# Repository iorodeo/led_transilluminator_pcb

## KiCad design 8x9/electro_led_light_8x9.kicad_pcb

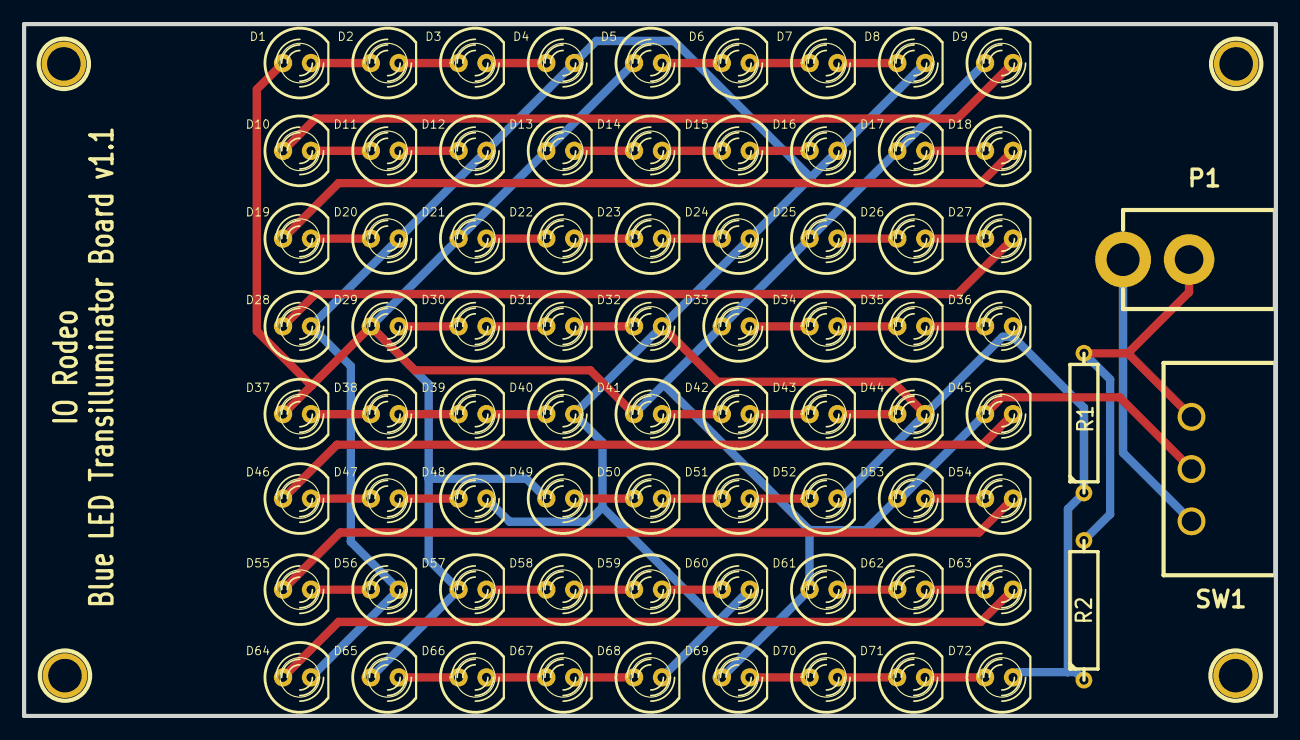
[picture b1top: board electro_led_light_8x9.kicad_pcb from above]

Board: 2 copper layers, 113.8 x 62.9 mm, 80 parts (0 on the bottom side), 58 nets.

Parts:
D1, D2, D3, D4, D5, D6, D7, D8, D9, D10, D11, D12, D13, D14, D15, D16, D17, D18, D19, D20, D21, D22, D23, D24, D25, D26, D27, D28, D29, D30, D31, D32, D33, D34, D35, D36, D37, D38, D39, D40, D41, D42, D43, D44, D45, D46, D47, D48, D49, D50, D51, D52, D53, D54, D55, D56, D57, D58, D59, D60, D61, D62, D63, D64, D65, D66, D67, D68, D69, D70, D71, D72: LED; CUSTOM2 LED-5MM
M1, M2, M3, M4: P***; 1pin
P1: CONN_2; DCJACK_2PIN
R1, R2: R; R5
SW1: SWITCH_INV; slide_switch

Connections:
/15V: P1.1, SW1.1
GND: P1.2, R1.2, R2.2, SW1.3
unnamed: D1.2, D2.1
unnamed: D25.2, D26.1
unnamed: D9.2, D10.1
unnamed: D10.2, D11.1
unnamed: D11.2, D12.1
unnamed: D15.2, D16.1
unnamed: D14.2, D15.1
unnamed: D13.2, D14.1
unnamed: D5.2, D6.1
unnamed: D6.2, D7.1
unnamed: D7.2, D8.1
unnamed: D3.2, D4.1
unnamed: D2.2, D3.1
unnamed: D4.2, D8.2, D12.2, D16.2, D20.2, D24.2, D28.2, D32.2, D36.2, D40.2, D44.2, D48.2, D52.2, D56.2, D60.2, D64.2, D68.2, D72.2, R1.1, R2.1
unnamed: D1.1, D5.1, D9.1, D13.1, D17.1, D21.1, D25.1, D29.1, D33.1, D37.1, D41.1, D45.1, D49.1, D53.1, D57.1, D61.1, D65.1, D69.1, SW1.2
unnamed: D69.2, D70.1
unnamed: D33.2, D34.1
unnamed: D34.2, D35.1
unnamed: D35.2, D36.1
unnamed: D39.2, D40.1
unnamed: D38.2, D39.1
unnamed: D37.2, D38.1
unnamed: D45.2, D46.1
unnamed: D46.2, D47.1
unnamed: D47.2, D48.1
unnamed: D43.2, D44.1
unnamed: D42.2, D43.1
unnamed: D41.2, D42.1
unnamed: D67.2, D68.1
unnamed: D66.2, D67.1
unnamed: D65.2, D66.1
unnamed: D71.2, D72.1
unnamed: D70.2, D71.1
unnamed: D49.2, D50.1
unnamed: D17.2, D18.1
unnamed: D18.2, D19.1
unnamed: D19.2, D20.1
unnamed: D23.2, D24.1
unnamed: D22.2, D23.1
unnamed: D21.2, D22.1
unnamed: D29.2, D30.1
unnamed: D30.2, D31.1
unnamed: D31.2, D32.1
unnamed: D27.2, D28.1
unnamed: D26.2, D27.1
unnamed: D57.2, D58.1
unnamed: D58.2, D59.1
unnamed: D59.2, D60.1
unnamed: D63.2, D64.1
unnamed: D62.2, D63.1
unnamed: D61.2, D62.1
unnamed: D53.2, D54.1
unnamed: D54.2, D55.1
unnamed: D55.2, D56.1
unnamed: D51.2, D52.1
unnamed: D50.2, D51.1

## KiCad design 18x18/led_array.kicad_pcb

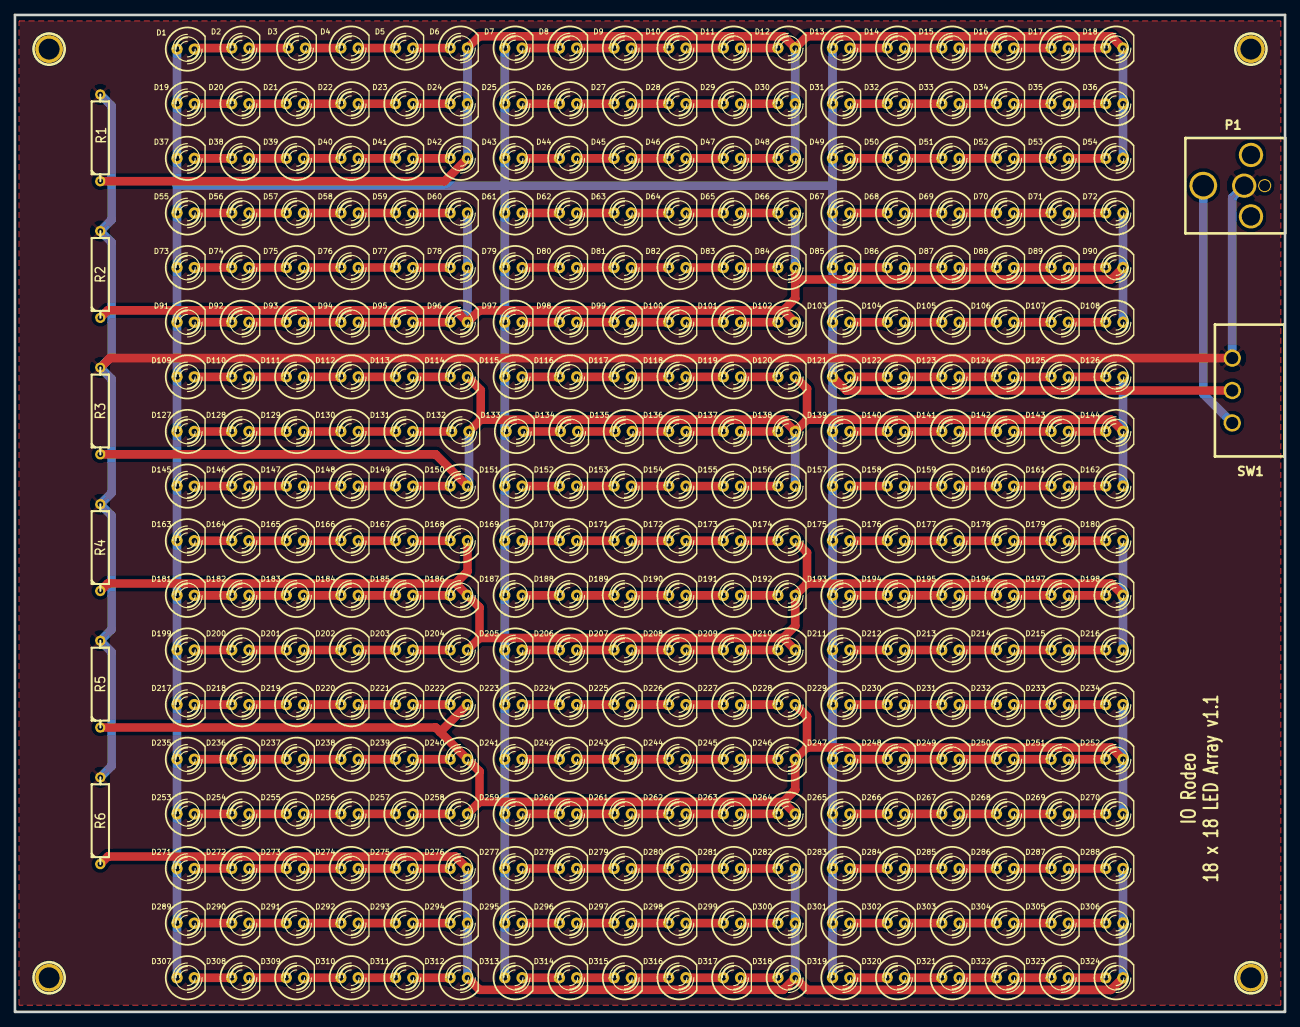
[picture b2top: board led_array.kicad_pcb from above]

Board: 2 copper layers, 186.0 x 146.0 mm, 336 parts (0 on the bottom side), 279 nets.

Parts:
D1, D2, D3, D4, D5, D6, D7, D8, D9, D10, D11, D12, D13, D14, D15, D16, D17, D18, D19, D20, D21, D22, D23, D24, D25, D26, D27, D28, D29, D30, D31, D32, D33, D34, D35, D36, D37, D38, D39, D40, D41, D42, D43, D44, D45, D46, D47, D48, D49, D50, D51, D52, D53, D54, D55, D56, D57, D58, D59, D60, D61, D62, D63, D64, D65, D66, D67, D68, D69, D70, D71, D72, D73, D74, D75, D76, D77, D78, D79, D80, D81, D82, D83, D84, D85, D86, D87, D88, D89, D90, D91, D92, D93, D94, D95, D96, D97, D98, D99, D100, D101, D102, D103, D104, D105, D106, D107, D108, D109, D110, D111, D112, D113, D114, D115, D116, D117, D118, D119, D120, D121, D122, D123, D124, D125, D126, D127, D128, D129, D130, D131, D132, D133, D134, D135, D136, D137, D138, D139, D140, D141, D142, D143, D144, D145, D146, D147, D148, D149, D150, D151, D152, D153, D154, D155, D156, D157, D158, D159, D160, D161, D162, D163, D164, D165, D166, D167, D168, D169, D170, D171, D172, D173, D174, D175, D176, D177, D178, D179, D180, D181, D182, D183, D184, D185, D186, D187, D188, D189, D190, D191, D192, D193, D194, D195, D196, D197, D198, D199, D200, D201, D202, D203, D204, D205, D206, D207, D208, D209, D210, D211, D212, D213, D214, D215, D216, D217, D218, D219, D220, D221, D222, D223, D224, D225, D226, D227, D228, D229, D230, D231, D232, D233, D234, D235, D236, D237, D238, D239, D240, D241, D242, D243, D244, D245, D246, D247, D248, D249, D250, D251, D252, D253, D254, D255, D256, D257, D258, D259, D260, D261, D262, D263, D264, D265, D266, D267, D268, D269, D270, D271, D272, D273, D274, D275, D276, D277, D278, D279, D280, D281, D282, D283, D284, D285, D286, D287, D288, D289, D290, D291, D292, D293, D294, D295, D296, D297, D298, D299, D300, D301, D302, D303, D304, D305, D306, D307, D308, D309, D310, D311, D312, D313, D314, D315, D316, D317, D318, D319, D320, D321, D322, D323, D324: LED; CUSTOM2 LED-5MM
M1, M2, M3, M4: P***; 1pin
P1: CONN_2; DCJACK_2PIN_HIGHCURRENT
R1, R2, R3, R4, R5, R6: R; R5
SW1: SWITCH_INV; slide_switch

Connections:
/15V: P1.1, SW1.1
GND: P1.2, R1.2, R2.2, R3.2, R4.2, R5.2, R6.2, SW1.3
unnamed: D265.2, D266.1
unnamed: D266.2, D267.1
unnamed: D267.2, D268.1
unnamed: D191.2, D192.1
unnamed: D202.2, D203.1
unnamed: D203.2, D204.1
unnamed: D197.2, D198.1
unnamed: D196.2, D197.1
unnamed: D172.2, D173.1
unnamed: D173.2, D174.1
unnamed: D179.2, D180.1
unnamed: D178.2, D179.1
unnamed: D166.2, D167.1
unnamed: D167.2, D168.1
unnamed: D214.2, D215.1
unnamed: D215.2, D216.1
unnamed: D208.2, D209.1
unnamed: D209.2, D210.1
unnamed: D253.2, D254.1
unnamed: D254.2, D255.1
unnamed: D229.2, D230.1
unnamed: D230.2, D231.1
unnamed: D231.2, D232.1
unnamed: D232.2, D233.1
unnamed: D237.2, D238.1
unnamed: D238.2, D239.1
unnamed: D236.2, D237.1
unnamed: D235.2, D236.1
unnamed: D223.2, D224.1
unnamed: D224.2, D225.1
unnamed: D225.2, D226.1
unnamed: D226.2, D227.1
unnamed: D219.2, D220.1
unnamed: D268.2, D269.1
unnamed: D241.2, D242.1
unnamed: D242.2, D243.1
unnamed: D243.2, D244.1
unnamed: D244.2, D245.1
unnamed: D249.2, D250.1
unnamed: D250.2, D251.1
unnamed: D248.2, D249.1
unnamed: D247.2, D248.1
unnamed: D259.2, D260.1
unnamed: D260.2, D261.1
unnamed: D261.2, D262.1
unnamed: D262.2, D263.1
unnamed: D255.2, D256.1
unnamed: D256.2, D257.1
unnamed: D188.2, D189.1
unnamed: D189.2, D190.1
unnamed: D190.2, D191.1
unnamed: D195.2, D196.1
unnamed: D194.2, D195.1
unnamed: D193.2, D194.1
unnamed: D205.2, D206.1
unnamed: D206.2, D207.1
unnamed: D207.2, D208.1
unnamed: D201.2, D202.1
unnamed: D200.2, D201.1
unnamed: D199.2, D200.1
unnamed: D168.2, D174.2, D180.2, D186.2, D192.2, D198.2, D204.2, D210.2, D216.2, R4.1
unnamed: D211.2, D212.1
unnamed: D212.2, D213.1
unnamed: D213.2, D214.1
unnamed: D187.2, D188.1
unnamed: D163.2, D164.1
unnamed: D184.2, D185.1
unnamed: D185.2, D186.1
unnamed: D175.2, D176.1
unnamed: D176.2, D177.1
unnamed: D177.2, D178.1
unnamed: D183.2, D184.1
unnamed: D182.2, D183.1
unnamed: D181.2, D182.1
unnamed: D169.2, D170.1
unnamed: D170.2, D171.1
unnamed: D171.2, D172.1
unnamed: D165.2, D166.1
unnamed: D164.2, D165.1
unnamed: D278.2, D279.1
unnamed: D279.2, D280.1
unnamed: D280.2, D281.1
unnamed: D273.2, D274.1
unnamed: D274.2, D275.1
unnamed: D272.2, D273.1
unnamed: D271.2, D272.1
unnamed: D316.2, D317.1
unnamed: D309.2, D310.1
unnamed: D310.2, D311.1
unnamed: D308.2, D309.1
unnamed: D307.2, D308.1
unnamed: D283.2, D284.1
unnamed: D284.2, D285.1
unnamed: D285.2, D286.1
unnamed: D286.2, D287.1
unnamed: D291.2, D292.1
unnamed: D292.2, D293.1
unnamed: D290.2, D291.1
unnamed: D289.2, D290.1
unnamed: D277.2, D278.1
unnamed: D275.2, D276.1
unnamed: D322.2, D323.1
unnamed: D323.2, D324.1
unnamed: D317.2, D318.1
unnamed: D276.2, D282.2, D288.2, D294.2, D300.2, D306.2, D312.2, D318.2, D324.2, R6.1
unnamed: D293.2, D294.1
unnamed: D299.2, D300.1
unnamed: D298.2, D299.1
unnamed: D311.2, D312.1
unnamed: D305.2, D306.1
unnamed: D304.2, D305.1
unnamed: D281.2, D282.1
unnamed: D287.2, D288.1
unnamed: D239.2, D240.1
unnamed: D245.2, D246.1
unnamed: D257.2, D258.1
unnamed: D251.2, D252.1
unnamed: D227.2, D228.1
unnamed: D222.2, D228.2, D234.2, D240.2, D246.2, D252.2, D258.2, D264.2, D270.2, R5.1
unnamed: D233.2, D234.1
unnamed: D220.2, D221.1
unnamed: D221.2, D222.1
unnamed: D269.2, D270.1
unnamed: D218.2, D219.1
unnamed: D217.2, D218.1
unnamed: D319.2, D320.1
unnamed: D320.2, D321.1
unnamed: D321.2, D322.1
unnamed: D295.2, D296.1
unnamed: D296.2, D297.1
unnamed: D297.2, D298.1
unnamed: D303.2, D304.1
unnamed: D302.2, D303.1
unnamed: D301.2, D302.1
unnamed: D313.2, D314.1
unnamed: D314.2, D315.1
unnamed: D315.2, D316.1
unnamed: D263.2, D264.1
unnamed: D17.2, D18.1
unnamed: D4.2, D5.1
unnamed: D5.2, D6.1
unnamed: D52.2, D53.1
unnamed: D53.2, D54.1
unnamed: D46.2, D47.1
unnamed: D47.2, D48.1
unnamed: D22.2, D23.1
unnamed: D23.2, D24.1
unnamed: D29.2, D30.1
unnamed: D28.2, D29.1
unnamed: D40.2, D41.1
unnamed: D41.2, D42.1
unnamed: D35.2, D36.1
unnamed: D34.2, D35.1
unnamed: D10.2, D11.1
unnamed: D11.2, D12.1
unnamed: D16.2, D17.1
unnamed: D85.2, D86.1
unnamed: D97.2, D98.1
unnamed: D98.2, D99.1
unnamed: D99.2, D100.1
unnamed: D100.2, D101.1
unnamed: D93.2, D94.1
unnamed: D94.2, D95.1
unnamed: D92.2, D93.1
unnamed: D91.2, D92.1
unnamed: D67.2, D68.1
unnamed: D68.2, D69.1
unnamed: D69.2, D70.1
unnamed: D70.2, D71.1
unnamed: D75.2, D76.1
unnamed: D76.2, D77.1
unnamed: D74.2, D75.1
unnamed: D103.2, D104.1
unnamed: D104.2, D105.1
unnamed: D105.2, D106.1
unnamed: D106.2, D107.1
unnamed: D79.2, D80.1
unnamed: D80.2, D81.1
unnamed: D81.2, D82.1
unnamed: D82.2, D83.1
unnamed: D87.2, D88.1
unnamed: D88.2, D89.1
unnamed: D86.2, D87.1
unnamed: D27.2, D28.1
unnamed: D33.2, D34.1
unnamed: D32.2, D33.1
unnamed: D31.2, D32.1
unnamed: D43.2, D44.1
unnamed: D44.2, D45.1
unnamed: D45.2, D46.1
unnamed: D39.2, D40.1
unnamed: D38.2, D39.1
unnamed: D37.2, D38.1
unnamed: D13.2, D14.1
unnamed: D6.2, D12.2, D18.2, D24.2, D30.2, D36.2, D42.2, D48.2, D54.2, R1.1
unnamed: D49.2, D50.1
unnamed: D50.2, D51.1
unnamed: D51.2, D52.1
unnamed: D25.2, D26.1
unnamed: D26.2, D27.1
unnamed: D14.2, D15.1
unnamed: D15.2, D16.1
unnamed: D21.2, D22.1
unnamed: D20.2, D21.1
unnamed: D19.2, D20.1
unnamed: D7.2, D8.1
unnamed: D8.2, D9.1
unnamed: D9.2, D10.1
unnamed: D3.2, D4.1
unnamed: D2.2, D3.1
unnamed: D1.2, D2.1
unnamed: D124.2, D125.1
unnamed: D129.2, D130.1
unnamed: D130.2, D131.1
unnamed: D128.2, D129.1
unnamed: D127.2, D128.1
unnamed: D115.2, D116.1
unnamed: D116.2, D117.1
unnamed: D117.2, D118.1
unnamed: D118.2, D119.1
unnamed: D111.2, D112.1
unnamed: D112.2, D113.1
unnamed: D110.2, D111.1
unnamed: D109.2, D110.1
unnamed: D140.2, D141.1
unnamed: D141.2, D142.1
unnamed: D139.2, D140.1
unnamed: D151.2, D152.1
unnamed: D152.2, D153.1
unnamed: D153.2, D154.1
unnamed: D154.2, D155.1
unnamed: D147.2, D148.1
unnamed: D148.2, D149.1
unnamed: D146.2, D147.1
unnamed: D145.2, D146.1
unnamed: D121.2, D122.1
unnamed: D122.2, D123.1
unnamed: D123.2, D124.1
unnamed: D143.2, D144.1
unnamed: D142.2, D143.1
unnamed: D119.2, D120.1
unnamed: D125.2, D126.1
unnamed: D113.2, D114.1
unnamed: D160.2, D161.1
unnamed: D161.2, D162.1
unnamed: D155.2, D156.1
unnamed: D114.2, D120.2, D126.2, D132.2, D138.2, D144.2, D150.2, D156.2, D162.2, R3.1
unnamed: D131.2, D132.1
unnamed: D137.2, D138.1
unnamed: D136.2, D137.1
unnamed: D149.2, D150.1
unnamed: D1.1, D7.1, D13.1, D19.1, D25.1, D31.1, D37.1, D43.1, D49.1, D55.1, D61.1, D67.1, D73.1, D79.1, D85.1, D91.1, D97.1, D103.1, D109.1, D115.1, D121.1, D127.1, D133.1, D139.1, D145.1, D151.1, D157.1, D163.1, D169.1, D175.1, D181.1, D187.1, D193.1, D199.1, D205.1, D211.1, D217.1, D223.1, D229.1, D235.1, D241.1, D247.1, D253.1, D259.1, D265.1, D271.1, D277.1, D283.1, D289.1, D295.1, D301.1, D307.1, D313.1, D319.1, SW1.2
unnamed: D77.2, D78.1
unnamed: D83.2, D84.1
unnamed: D60.2, D66.2, D72.2, D78.2, D84.2, D90.2, D96.2, D102.2, D108.2, R2.1
unnamed: D95.2, D96.1
unnamed: D89.2, D90.1
unnamed: D64.2, D65.1
unnamed: D73.2, D74.1
unnamed: D61.2, D62.1
unnamed: D62.2, D63.1
unnamed: D63.2, D64.1
unnamed: D57.2, D58.1
unnamed: D58.2, D59.1
unnamed: D56.2, D57.1
unnamed: D55.2, D56.1
unnamed: D157.2, D158.1
unnamed: D158.2, D159.1
unnamed: D159.2, D160.1
unnamed: D133.2, D134.1
unnamed: D134.2, D135.1
unnamed: D135.2, D136.1
unnamed: D65.2, D66.1
unnamed: D71.2, D72.1
unnamed: D59.2, D60.1
unnamed: D107.2, D108.1
unnamed: D101.2, D102.1

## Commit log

2012-06-26 Project creation.
2012-06-26 Add license.
2012-08-29 Added board changes.
2012-09-13 Modified PCB to include switch. Created new Gerber files for v1.1. Added BOM.
2012-10-10 Modified BOM.
2012-10-22 Fixed BOM for PCB with correct part number for the 2.1mm connector.
2013-10-29 Created 8x9 sub-directory and moved current set of files into it
2013-10-29 Renamed gerner_v1p1 gerber_v1p1.
2013-10-29 Fixed error in gerber_v1p1 zip package name.
2013-10-29 Addd new directory for 9x12 pcb.
2013-11-15 Layout of components on the 9x16 PCB.
2013-11-15 Renamed folder to 9x16.
2013-11-15 Created a 16x16 led array project.
2013-11-15 Modified design to a 9x18 LED array.
2013-11-16 Layout of additioanl LEDs in the 18x18 array.
2013-11-18 Finished layout and routing of 9x18 and 18x18 led arrays.
2013-11-19 Created Gerber files for 9x18 and 18x18 led arrays.
2014-01-12 Minor changes.
2014-01-12 Updated the BOM or all 3 boards.
2016-12-06 Added position placement files for 8x9 mini transilluminator.
